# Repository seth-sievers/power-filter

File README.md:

# power-filter
A basic pcb to filter high frequency noise and regulate voltage for sensitive instrumentation

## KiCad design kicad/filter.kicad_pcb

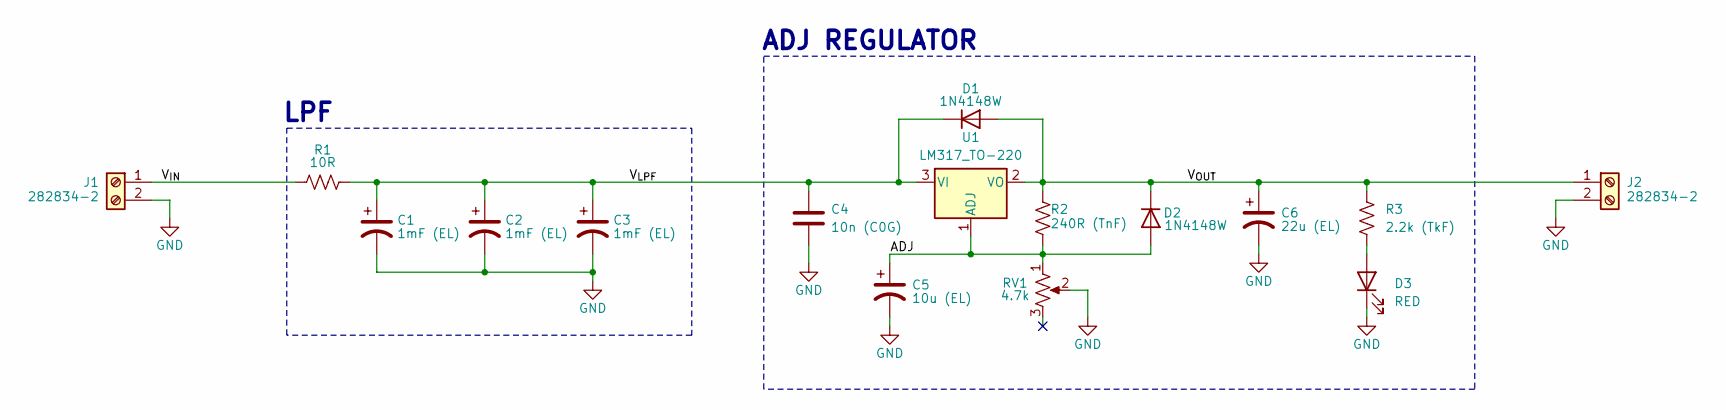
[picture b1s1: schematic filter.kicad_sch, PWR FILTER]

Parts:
C1, C2, C3: 1mF (EL); CP_Radial_D12.5mm_P5.00mm
C4: 10n (C0G); C_0603_1608Metric
C5: 10u (EL); CP_Radial_D5.0mm_P2.00mm
C6: 22u (EL); CP_Radial_D5.0mm_P2.50mm
D1, D2: 1N4148W; D_SOD-323
D3: RED; LED_D5.0mm
J1, J2: 282834-2; TerminalBlock_TE_282834-2_1x02_P2.54mm_Horizontal
R1: 10R; R_Axial_DIN0617_L17.0mm_D6.0mm_P30.48mm_Horizontal
R2: 240R (TnF); C_0603_1608Metric
R3: 2.2k (TkF); R_1210_3225Metric
RV1: 4.7k; Potentiometer_Bourns_3386P_Vertical
U1: LM317_TO-220; TO-220-3_Horizontal_TabDown

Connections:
/ADJ: C5.1, D2.2 (A), R2.1, RV1.1, U1.1 (ADJ)
/V_{IN}: J1.1, R1.1
/V_{LPF}: C1.1, C2.1, C3.1, C4.1, D1.1 (K), R1.2, U1.3 (VI)
/V_{OUT}: C6.1, D1.2 (A), D2.1 (K), J2.1, R2.2, R3.1, U1.2 (VO)
GND: C1.2, C2.2, C3.2, C4.2, C5.2, C6.2, D3.1 (K), J1.2, J2.2, RV1.2
unnamed: D3.2 (A), R3.2

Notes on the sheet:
ADJ REGULATOR
LPF

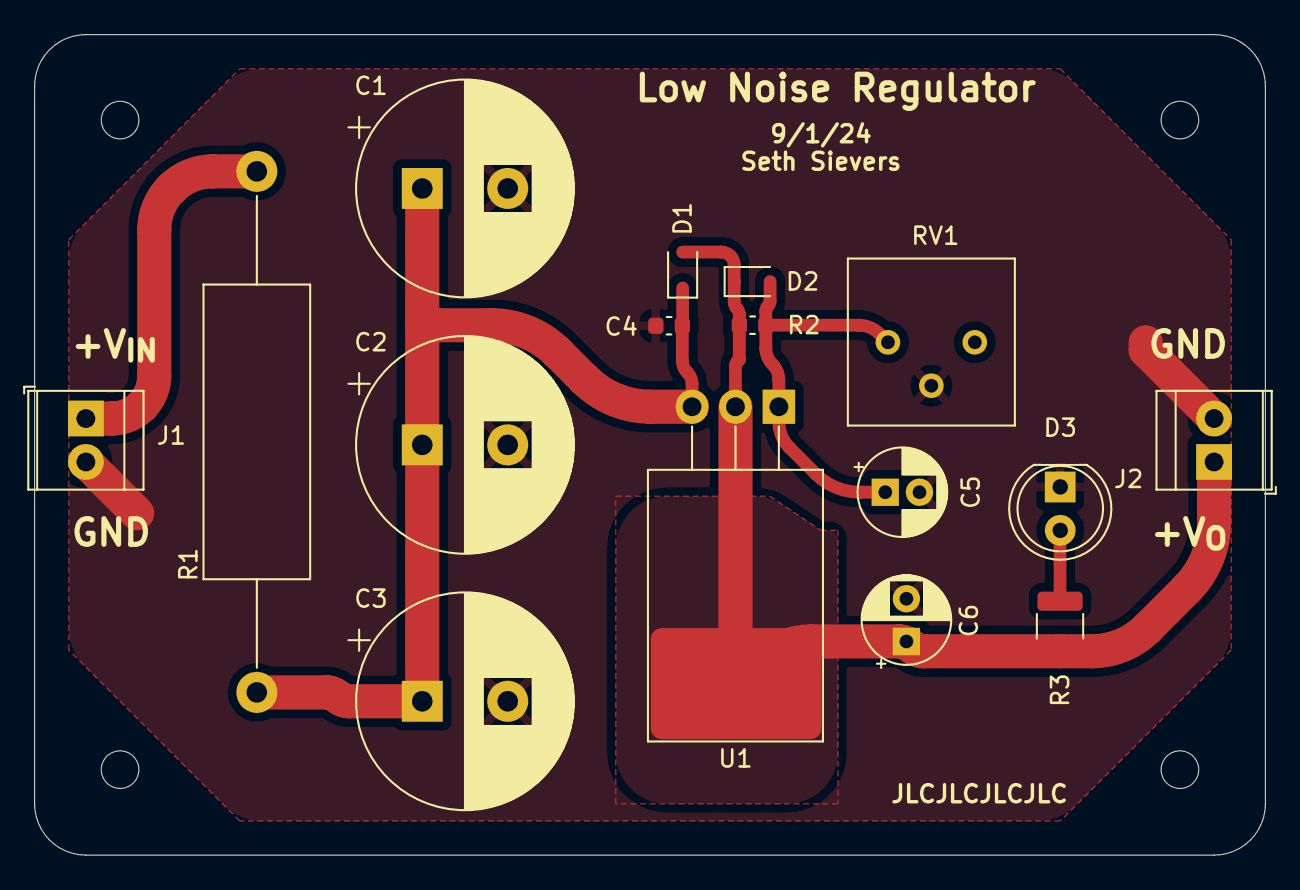
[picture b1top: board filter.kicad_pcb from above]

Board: 2 copper layers, 72.0 x 48.0 mm, 16 parts (0 on the bottom side), 6 nets.

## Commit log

2024-09-01 ordered
2024-10-15 sync changes
